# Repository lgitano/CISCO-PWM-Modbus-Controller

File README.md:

# CISCO AA23200 (3000W) PWM & Modbus RTU Controller

A galvanically isolated **Modbus RTU**, **31 kHz Buck-PWM Fan Controller**, **4-Channel NTC Temperature Monitor**, and **I²C Telemetry Interface** designed to retrofit **Cisco / Astec AA23200 3000W Server PSUs** for CNC machines, lab power supplies, and industrial control cabinets. 

This project was heavily inspired by this thread: https://forum.mosfetkiller.de/viewtopic.php?t=64061 and developed with AI assistance.

---

## Features

- **Cisco ADM1041 I²C Telemetry Bridge (`CN940`):**
  - Direct connection to the PSU's internal `ADM1041` controller (`SDA`, `SCL`, `SGND`) for reading PSU status, voltages, currents, and fault flags. As well as writing Voltages from 41.1V to approx. 51V via registers in temporary RAM
- **2× High-Current 31 kHz Buck-PWM Fan Channels (`FAN1`, `FAN2`):**
  - Driven by logic-level `IRLZ44N` N-MOSFETs (`Q4`, `Q5`) with `47 µH` toroidal inductors (`L1`, `L2`), `SB340` Schottky freewheeling diodes (`D3`, `D4`), and `220 µF` low-ESR output capacitors (`C9`, `C10`) for smooth DC-like voltage control of high-power server fans (up to 3 A+ per channel) without PWM whine.
- **Galvanically Isolated RS485 / Modbus RTU & E-Stop:**
  - Full galvanic isolation (`~2.5 mm` creepage/clearance trench) between PSU logic (`GND` / `+5V`) and external control cabinet bus (`/ISO_GND` / `/ISO_5V`) via a `B0505S-1WR3` isolated DC/DC converter (`J12`) and 4× `PC817` optocouplers (`U1`–`U4`).
  - Bidirectional TVS diode transient protection (`P6KE6.8CA`, `D1`/`D2`) on RS485 `A`/`B` lines and `1N4148` clamping (`D5`) on the isolated E-Stop input.
- **4× NTC Thermistor Inputs (`NTC1`–`NTC4`):**
  - `10 kΩ` (1%) precision voltage dividers (`R2`–`R5`) with `100 nF` hardware low-pass filtering (`C1`–`C4`) on `A0`–`A3`.
- **Open-Drain Tacho Output (`D2` / `Q1`):**
  - `2N7000` open-drain driver (`Q1`) to feed a simulated fan tachometer signal (`~200 Hz`) back to the Cisco mainboard so the green **FAN OK** LED stays active after replacing the stock fan. 
- **Expansion Headers:**
  - `AUX_IN` (`A6`, `A7` with `1 kΩ` series protection) and `AUX_SPI` (`MOSI`, `MISO`, `SCK`, `+5V`) for external displays, sensors, or additional I/O.

---

## Repository Structure

```text
├── Hardware/          # KiCad 10 project (.kicad_sch, .kicad_pcb), Gerbers, BOM & FreeCAD 3D carrier
├── Software/          # Arduino Nano firmware (31 kHz PWM, NTC Steinhart-Hart, Modbus RTU, ADM1041 I2C)
├── media/             # pictures and documentation
└── README.md          # Project documentation & pinout reference
```

---

## Hardware Pinout & Connectors (PCB v1.4)

All board connectors use **2.50 mm JST-XH** headers unless noted otherwise.

### Power & Fan Outputs (Top Edge)

| Connector | Label | Pin 1 | Pin 2 | Pin 3 | Pin 4 | Notes |
| :--- | :--- | :--- | :--- | :--- | :--- | :--- |
| **`J9`** | `-  +  T  FAN1` | `FAN1-` (Buck GND) | `+12V` | `D2` (Tacho) | `D6` | Channel 1 Buck-PWM (`D9` -> `Q4`) |
| **`J11`** | `-12V+` | `GND` | `+12V` | — | — | Main 12 V supply from Cisco PSU |
| **`J10`** | `-  +  T  FAN2` | `FAN2-` (Buck GND) | `+12V` | `D7` | `D8` | Channel 2 Buck-PWM (`D10` -> `Q5`) |

### Sensors, Telemetry & Isolated Field Bus (Left Edge)

| Connector | Label | Pin 1 | Pin 2 | Pin 3 | Pin 4 | Notes |
| :--- | :--- | :--- | :--- | :--- | :--- | :--- |
| **`J1`** | `NTC1` | `A1` | `GND` | — | — | 10 kΩ NTC input (`R3`, `C2`) |
| **`J2`** | `NTC2` | `A2` | `GND` | — | — | 10 kΩ NTC input (`R4`, `C3`) |
| **`J3`** | `NTC3` | `A0` | `GND` | — | — | 10 kΩ NTC input (`R2`, `C1`) |
| **`J4`** | `NTC4` | `A3` | `GND` | — | — | 10 kΩ NTC input (`R5`, `C4`) |
| **`J5`** | `TACHO` | `Q1 Drain` (`D2`) | `NC` | — | — | Open-drain tacho signal to Cisco |
| **`J7`** | `- CN940-I2C` | `GND` (`SGND`) | `SCL` (`A5`) | `SDA` (`A4`) | — | Connects to Cisco `CN940` header |
| **`J18`** | `+ AUXIN -` | `+5V` | `A6` (1 kΩ) | `A7` (1 kΩ) | `GND` | Auxiliary analog inputs |
| **`J13`** | `- 5V +` | `GND` | `+5V` | — | — | 5 V standby supply from Cisco PSU |
| **`J14`** | `- E-STOP` | `/ISO_GND` | `/ISO_ESTOP` | — | — | **Isolated** E-Stop loop (`U4` -> `D5`) |
| **`J17`** | `- RS485` | `/ISO_GND` | `RS485 B` | `RS485 A` | — | **Isolated** Modbus RTU bus (`TVS` protected) |

### Internal Headers

| Connector | Label | Pin 1 | Pin 2 | Pin 3 | Pin 4 | Notes |
| :--- | :--- | :--- | :--- | :--- | :--- | :--- |
| **`J19`** | `+ AUXSPI` | `+5V` | `MOSI` (`D11`) | `MISO` (`D12`) | `SCK` (`D13`) | Auxiliary SPI expansion |
| **`J12`** | `B0505S-1WR3` | `GND` | `+5V` | `/ISO_GND` | `/ISO_5V` | Isolated 5 V DC/DC converter |
| **`J6`/`J8`** | `ARDUINO NANO` | — | — | — | — | `15.24 mm` (600 mil) row spacing |
| **`J15`/`J16`** | `MAX485` | — | — | — | — | `40.64 mm` (1600 mil) row spacing |

---

## Cisco AA23200 Internal `CN940` I²C Wiring

The `CN940` connector on the Cisco AA23200 daughterboard is a 3-pin `2.50 mm` SMD shrouded header located near the rear bezel cutout:

```text
CN940 (looking into header, Pin 1 marked with white dot on the right):
[ Pin 3: SGND ]  [ Pin 2: SCL ]  [ Pin 1 (•): SDA ]
       │                │                 │
       ▼                ▼                 ▼
   J7 Pin 1         J7 Pin 2          J7 Pin 3
```

> **Tip:** Because `CN940` is an SMD header with narrow side slots, use individual heat-shrink-insulated `JST-XH` female crimp contacts secured with a small drop of hot glue / RTV silicone rather than forcing a standard `JST-XH` housing.

---

## Mechanical Integration

- **PCB Dimensions:** `64.92 mm × 106.68 mm` (2-layer FR-4, `1.6 mm`, `1 oz` copper)
- **Mounting Holes:** 4× `M3` (`Ø 3.2 mm`), spacing `46.46 mm × 98.00 mm`
- **Orientation:** Mounted horizontally (`90°` rotated) along the inner side wall via a custom **PETG/ASA 3D-printed carrier bracket** (`Hardware/`), maintaining generous clearance to the overhead 320–400 V PFC choke and separating the main backplane wiring harness from the JST connectors.

---

## Safety Notice

⚠️ **High Voltage Warning:** Opening a server power supply exposes mains voltage (`230 V AC`) and high-voltage DC bus capacitors (`320–400 V DC`). Always disconnect mains power, allow capacitors to discharge fully before working inside the chassis, and maintain adequate insulation barriers between the controller board and primary-side components.

---

## License

© 2026 El Gitano — Released for personal and open-source hardware use.

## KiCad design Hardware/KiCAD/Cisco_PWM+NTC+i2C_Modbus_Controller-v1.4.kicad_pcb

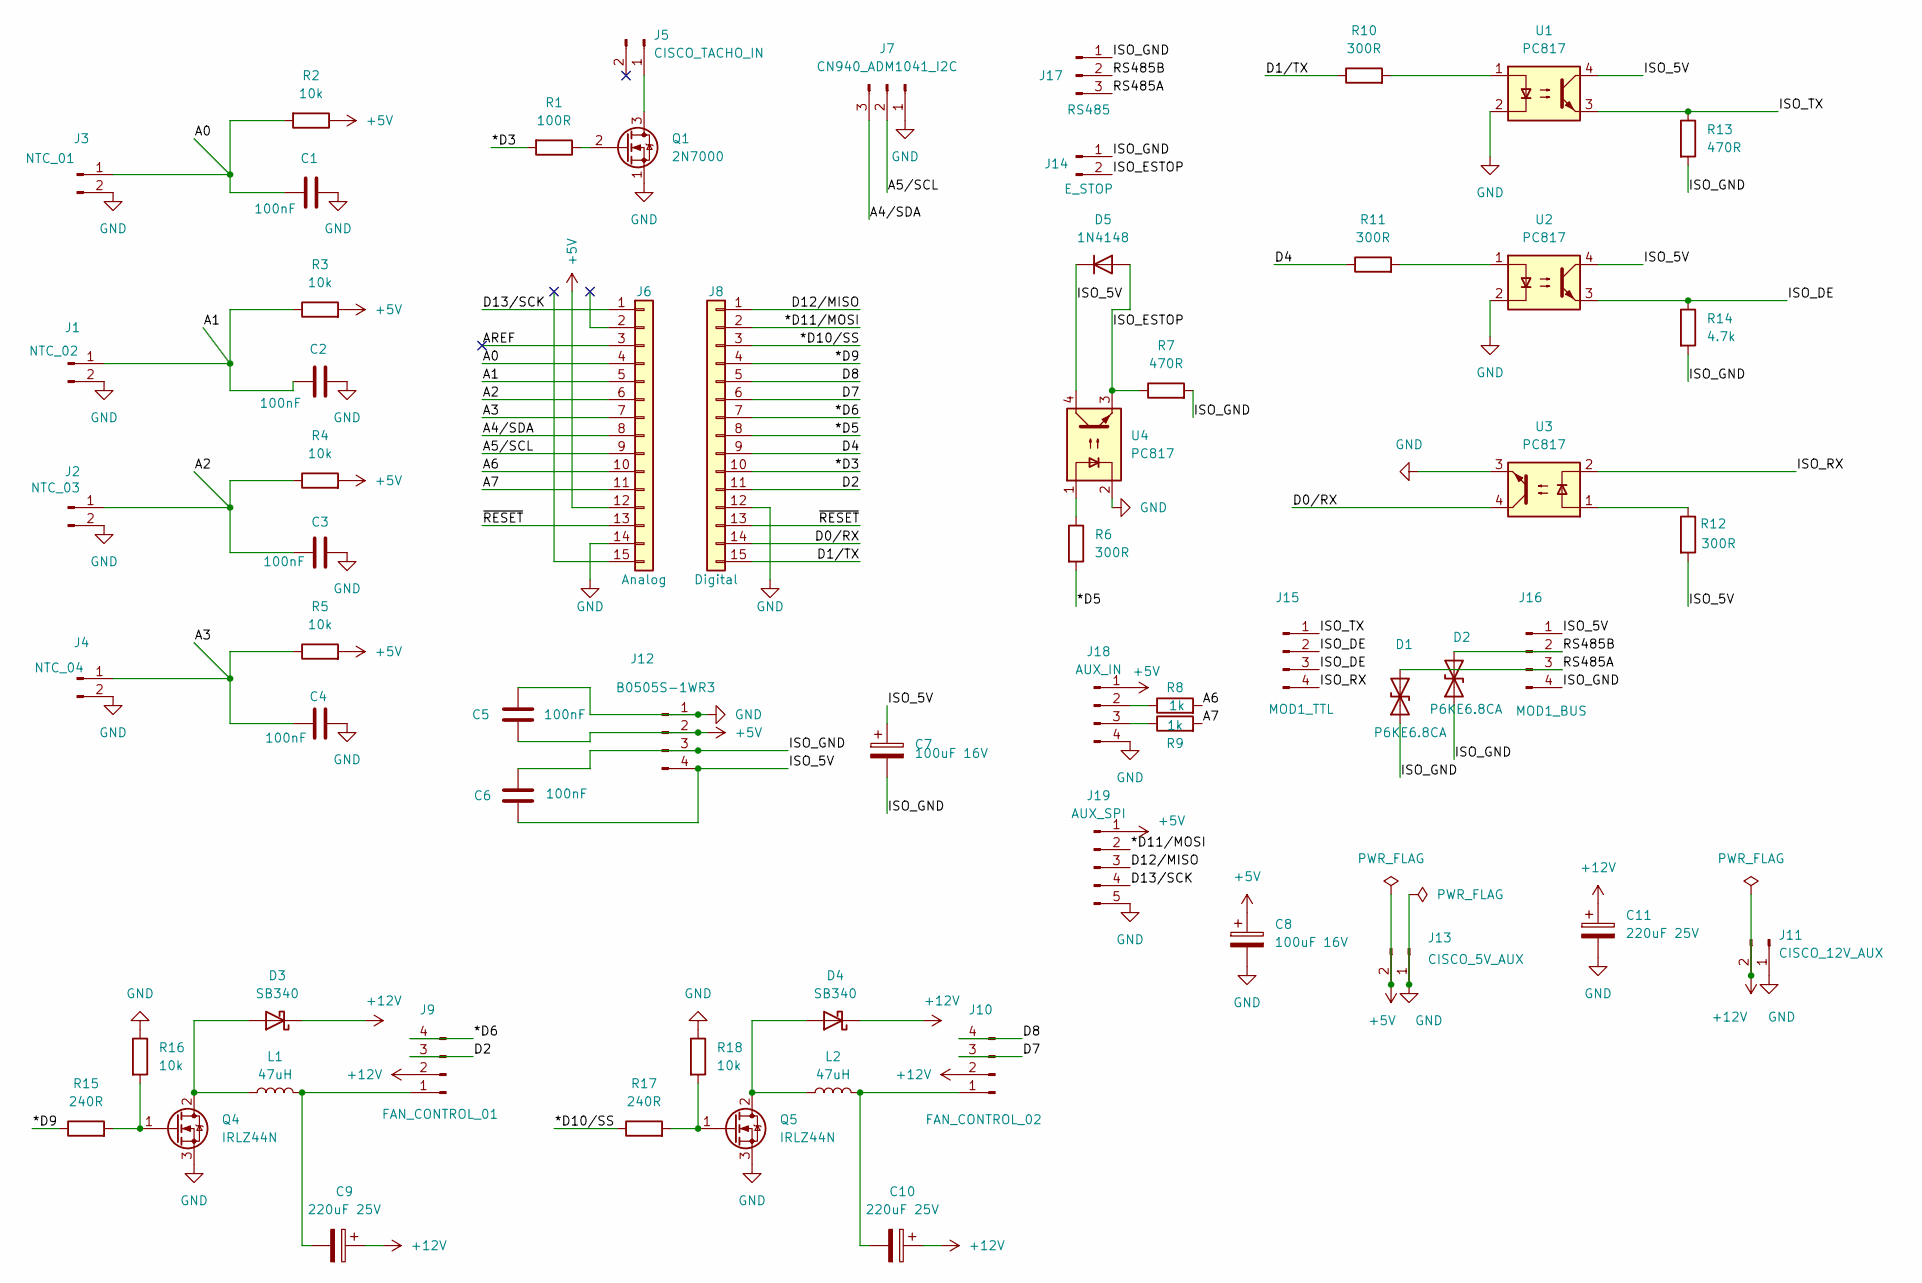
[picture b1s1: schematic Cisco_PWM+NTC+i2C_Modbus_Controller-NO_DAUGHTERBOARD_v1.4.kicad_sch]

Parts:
C1, C2, C3, C4, C5, C6: 100nF; C_Disc_D5.0mm_W2.5mm_P2.50mm
C7, C8: 100uF 16V; CP_Radial_D5.0mm_P2.00mm
C9, C10: 220uF 25V; CP_Radial_D8.0mm_P3.50mm
C11: 220uF 25V; CP_Radial_D10.0mm_P5.00mm
D1, D2: P6KE6.8CA; D_DO-15_P12.70mm_Horizontal
D3, D4: SB340; D_DO-201AD_P15.24mm_Horizontal
D5: 1N4148; D_DO-35_SOD27_P7.62mm_Horizontal
J1: NTC_02; JST_XH_B2B-XH-A_1x02_P2.50mm_Vertical
J2: NTC_03; JST_XH_B2B-XH-A_1x02_P2.50mm_Vertical
J3: NTC_01; JST_XH_B2B-XH-A_1x02_P2.50mm_Vertical
J4: NTC_04; JST_XH_B2B-XH-A_1x02_P2.50mm_Vertical
J5: CISCO_TACHO_IN; JST_XH_B2B-XH-A_1x02_P2.50mm_Vertical
J6: Analog; PinSocket_1x15_P2.54mm_Vertical
J7: CN940_ADM1041_I2C; JST_XH_B3B-XH-A_1x03_P2.50mm_Vertical
J8: Digital; PinSocket_1x15_P2.54mm_Vertical
J9: FAN_CONTROL_01; JST_XH_B4B-XH-A_1x04_P2.50mm_Vertical
J10: FAN_CONTROL_02; JST_XH_B4B-XH-A_1x04_P2.50mm_Vertical
J11: CISCO_12V_AUX; JST_XH_B2B-XH-A_1x02_P2.50mm_Vertical
J12: B0505S-1WR3; PinHeader_1x04_P2.54mm_Vertical
J13: CISCO_5V_AUX; JST_XH_B2B-XH-A_1x02_P2.50mm_Vertical
J14: E_STOP; JST_XH_B2B-XH-A_1x02_P2.50mm_Vertical
J15: MOD1_TTL; PinSocket_1x04_P2.54mm_Vertical
J16: MOD1_BUS; PinSocket_1x04_P2.54mm_Vertical
J17: RS485; JST_XH_B3B-XH-A_1x03_P2.50mm_Vertical
J18: AUX_IN; JST_XH_B4B-XH-A_1x04_P2.50mm_Vertical
J19: AUX_SPI; JST_XH_B4B-XH-A_1x04_P2.50mm_Vertical
L1, L2: 47uH; L_Toroid_Vertical_L14.7mm_W8.6mm_P5.58mm_Pulse_KM-1
Q1: 2N7000; TO-92_Inline
Q4, Q5: IRLZ44N; TO-220-3_Vertical
R1: 100R; R_Axial_DIN0207_L6.3mm_D2.5mm_P10.16mm_Horizontal
R2, R3, R4, R5, R16, R18: 10k; R_Axial_DIN0207_L6.3mm_D2.5mm_P2.54mm_Vertical
R6, R10, R11, R12: 300R; R_Axial_DIN0207_L6.3mm_D2.5mm_P10.16mm_Horizontal
R7, R13: 470R; R_Axial_DIN0207_L6.3mm_D2.5mm_P10.16mm_Horizontal
R8, R9: 1k; R_Axial_DIN0207_L6.3mm_D2.5mm_P2.54mm_Vertical
R14: 4.7k; R_Axial_DIN0207_L6.3mm_D2.5mm_P10.16mm_Horizontal
R15, R17: 240R; R_Axial_DIN0207_L6.3mm_D2.5mm_P2.54mm_Vertical
U1, U2, U3, U4: PC817; DIP-4_W7.62mm

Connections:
+5V: C5.2, C8.1, J6.12, J12.2, J13.2, J18.1, J19.1, R2.1, R3.2, R4.2, R5.2
+12V: C9.1, C10.1, C11.1, D3.1 (K), D4.1 (K), J9.2, J10.2, J11.2
/*D3: J8.10, R1.2
/*D5: J8.8, R6.2
/*D6: J8.7, J9.4
/*D9: J8.4, R15.1
/*D10/SS: J8.3, R17.1
/*D11/MOSI: J8.2, J19.2
/A0: C1.1, J3.1, J6.4, R2.2
/A1: C2.1, J1.1, J6.5, R3.1
/A2: C3.1, J2.1, J6.6, R4.1
/A3: C4.1, J4.1, J6.7, R5.1
/A4/SDA: J6.8, J7.3
/A5/SCL: J6.9, J7.2
/A6: J6.10, R8.2
/A7: J6.11, R9.2
/AREF: J6.3
/D0/RX: J8.14, U3.4
/D1/TX: J8.15, R10.1
/D2: J8.11, J9.3
/D4: J8.9, R11.1
/D7: J8.6, J10.3
/D8: J8.5, J10.4
/D12/MISO: J8.1, J19.3
/D13/SCK: J6.1, J19.4
/ISO_5V: C6.2, C7.1, D5.1 (K), J12.4, J16.1, R12.2, U1.4, U2.4, U4.4
/ISO_DE: J15.2, J15.3, R14.1, U2.3
/ISO_ESTOP: D5.2 (A), J14.2, R7.1, U4.3
/ISO_GND: C6.1, C7.2, D1.1 (A1), D2.1 (A1), J12.3, J14.1, J16.4, J17.1, R7.2, R13.2, R14.2
/ISO_RX: J15.4, U3.2
/ISO_TX: J15.1, R13.1, U1.3
/RS485A: D1.2 (A2), J16.3, J17.3
/RS485B: D2.2 (A2), J16.2, J17.2
/~RESET: J6.13, J8.13
GND: C1.2, C2.2, C3.2, C4.2, C5.1, C8.2, C11.2, J1.2, J2.2, J3.2, J4.2, J6.14, J7.1, J8.12, J11.1, J12.1, J13.1, J18.4, J19.5, Q1.1 (S), Q4.3 (S), Q5.3 (S), R16.1, R18.1, U1.2, U2.2, U3.3, U4.2
unnamed: D3.2 (A), L1.1, Q4.2 (D)
unnamed: D4.2 (A), L2.1, Q5.2 (D)
unnamed: J5.1 (Pin_1_1), Q1.3 (D)
unnamed: C9.2, J9.1, L1.2
unnamed: C10.2, J10.1, L2.2
unnamed: J18.2, R8.1
unnamed: J18.3, R9.1
unnamed: Q1.2 (G), R1.1
unnamed: Q4.1 (G), R15.2, R16.2
unnamed: Q5.1 (G), R17.2, R18.2
unnamed: R6.1, U4.1
unnamed: R10.2, U1.1
unnamed: R11.2, U2.1
unnamed: R12.1, U3.1

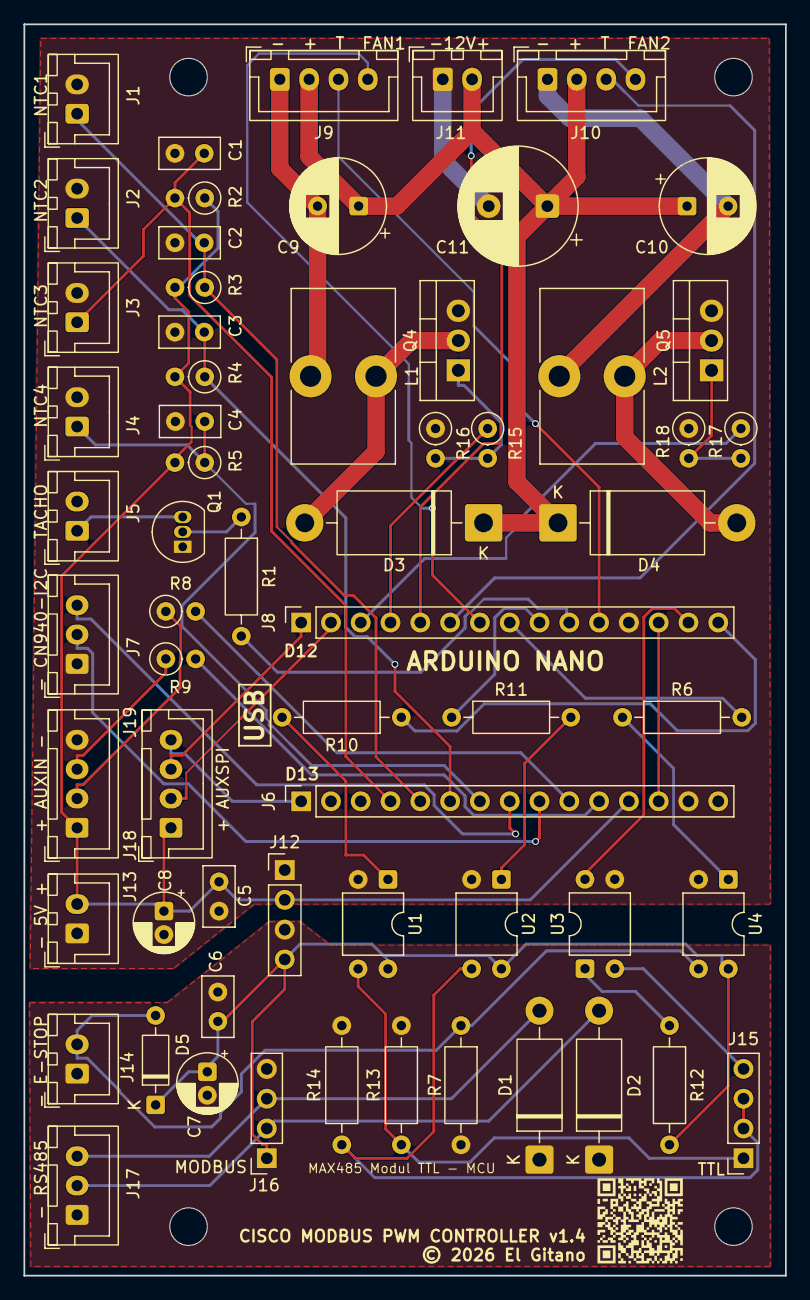
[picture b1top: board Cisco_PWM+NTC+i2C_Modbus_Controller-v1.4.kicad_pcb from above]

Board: 2 copper layers, 64.9 x 106.7 mm, 62 parts (0 on the bottom side), 48 nets.
